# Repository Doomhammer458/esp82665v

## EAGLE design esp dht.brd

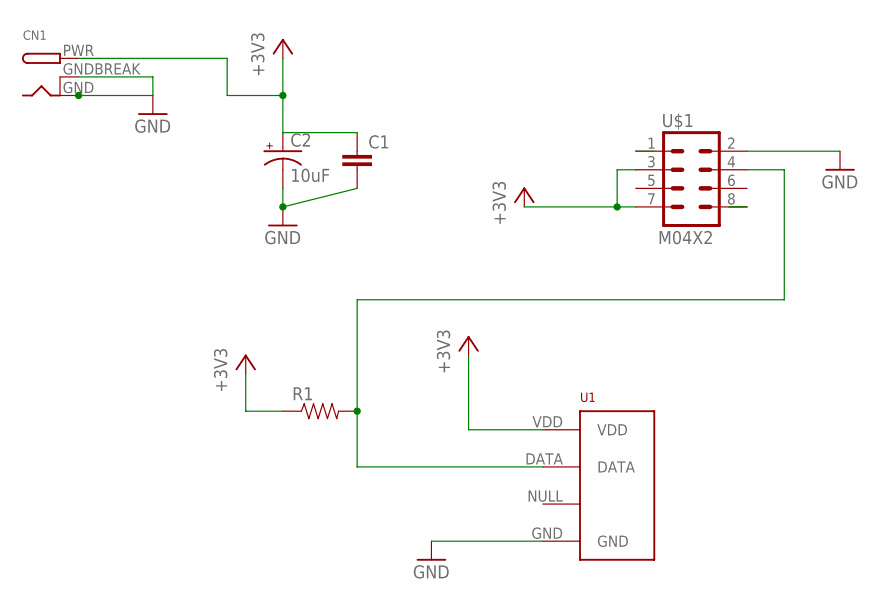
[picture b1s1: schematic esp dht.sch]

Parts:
C1: CAPPTH; CAP-PTH-SMALL
C2: 10uF; CPOL-RADIAL-10UF-25V
CN1: DCBARRELPTH; DCJACK_2MM_PTH
R1: RESISTORPTH-1/4W; AXIAL-0.4
U1: RHT03_DHT-22_AM2302RA; RHT03_DHT-22/RA
U$1: M04X2; 2X4

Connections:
+3V3: C1.1, C2.1 (+), CN1.PWR, R1.P$1 (1), U1.VDD, U$1.3, U$1.7
GND: C1.2, C2.2 (-), CN1.GND, CN1.GNDBREAK, U1.GND, U$1.2
unnamed: R1.P$2 (2), U1.DATA, U$1.4
TXL: U$1.1

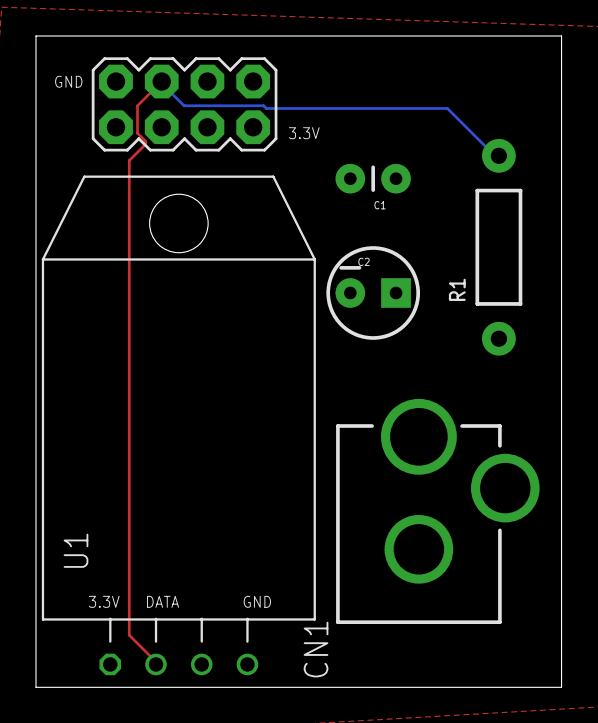
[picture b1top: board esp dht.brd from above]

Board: 2 copper layers, 29.2 x 36.2 mm, 6 parts (0 on the bottom side), 3 nets.

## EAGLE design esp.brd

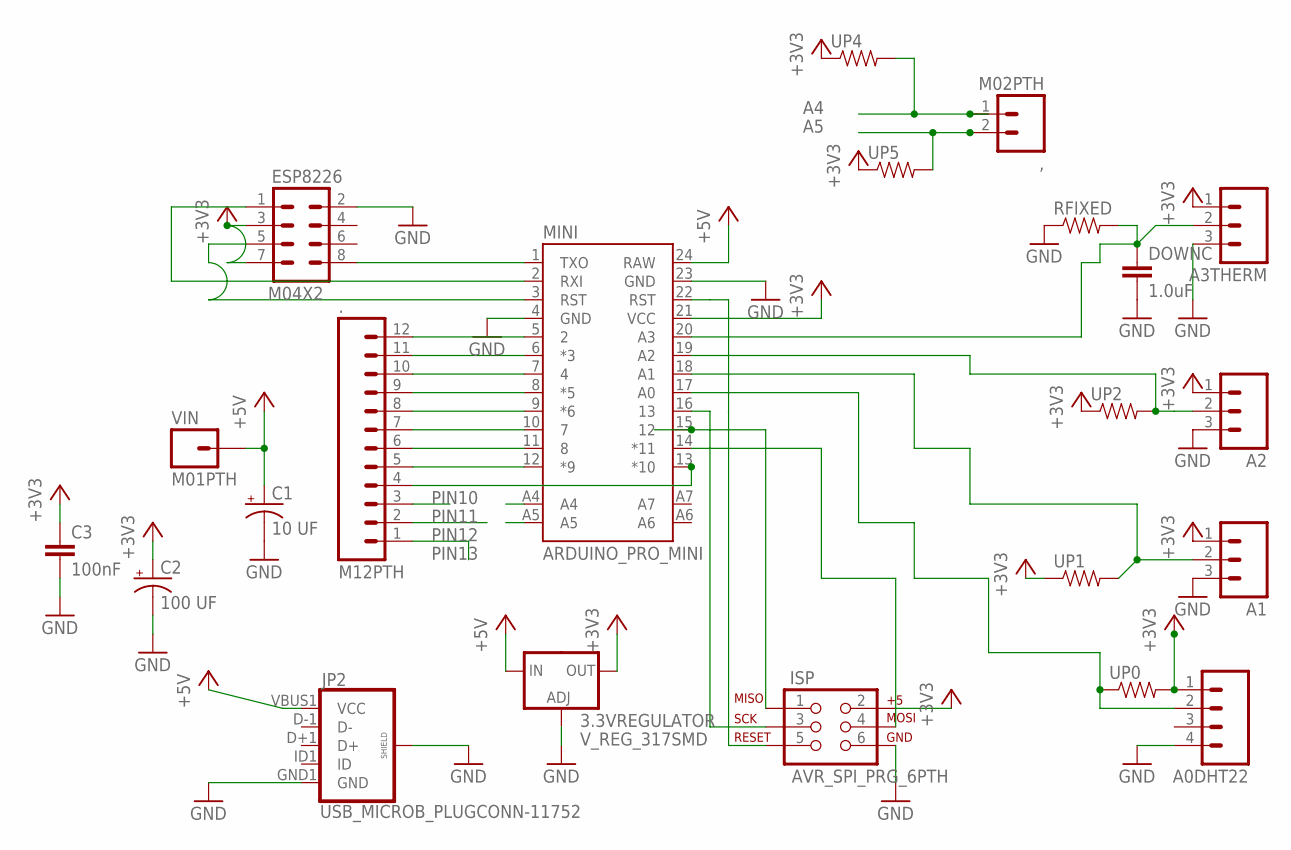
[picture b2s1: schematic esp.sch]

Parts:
3.3VREGULATOR: V_REG_317SMD; SOT223
,: M02PTH; 1X02
.: M12PTH; 1X12
A0DHT22: M04PTH; 1X04
A1, A2, A3THERM: M03PTH; 1X03
C1: 10 UF; CPOL-RADIAL-10UF-25V
C2: 100 UF; CPOL-RADIAL-10UF-25V
C3: 100nF; 0805
DOWNC: 1.0uF; 0805
ESP8226: M04X2; 2X4
ISP: AVR_SPI_PRG_6PTH; 2X3
JP2: USB_MICROB_PLUGCONN-11752; USB-B-MICRO-SMD_V03
MINI: ARDUINO_PRO_MINI
RFIXED: 0.3OHM-1/8W-1%(0805); 0805
UP0, UP1, UP2, UP4, UP5: 0.3OHM-1/8W-1%(0805); 0805
VIN: M01PTH; 1X01

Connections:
+3V3: 3.3VREGULATOR.2 (OUT), A0DHT22.1, A1.1, A2.1, A3THERM.1, C2.1 (+), C3.1, ESP8226.3, ESP8226.7, ISP.2, MINI.21 (VCC), UP0.2, UP1.1, UP2.1, UP4.1, UP5.1
+5V: 3.3VREGULATOR.3 (IN), C1.1 (+), JP2.VBUS1 (VCC), MINI.24 (RAW), VIN.1
A4: ,.1, MINI.A4, UP4.2
A5: ,.2, MINI.A5, UP5.2
GND: 3.3VREGULATOR.1 (ADJ), A0DHT22.4, A1.3, A2.3, A3THERM.3, C1.2 (-), C2.2 (-), C3.2, DOWNC.2, ESP8226.2, ISP.6, JP2.GND1 (GND), JP2.SHIELD1 (SHIELD), JP2.SHIELD2 (SHIELD), JP2.SHIELD3 (SHIELD), MINI.4 (GND), MINI.23 (GND), RFIXED.1
unnamed: ESP8226.1, MINI.2 (RXI)
unnamed: ESP8226.8, MINI.1 (TXO)
unnamed: A2.2, MINI.19 (A2), UP2.2
unnamed: A3THERM.2, DOWNC.1, MINI.20 (A3), RFIXED.2
unnamed: ..12, MINI.5 (2)
unnamed: A0DHT22.2, MINI.17 (A0), UP0.1
unnamed: ..11, MINI.6 (*3)
unnamed: ..10, MINI.7 (4)
unnamed: ..9, MINI.8 (*5)
unnamed: ..8, MINI.9 (*6)
unnamed: ..7, MINI.10 (7)
unnamed: ..6, MINI.11 (8)
unnamed: ..5, MINI.12 (*9)
unnamed: ESP8226.5, MINI.3 (RST)
unnamed: A1.2, MINI.18 (A1), UP1.2
PIN10: ..4, MINI.13 (*10)
PIN11: ..3, ISP.4, MINI.14 (*11)
PIN12: ..2, ISP.1, MINI.15 (12)
PIN13: ..1, ISP.3, MINI.16 (13)
RST: ISP.5, MINI.22 (RST)

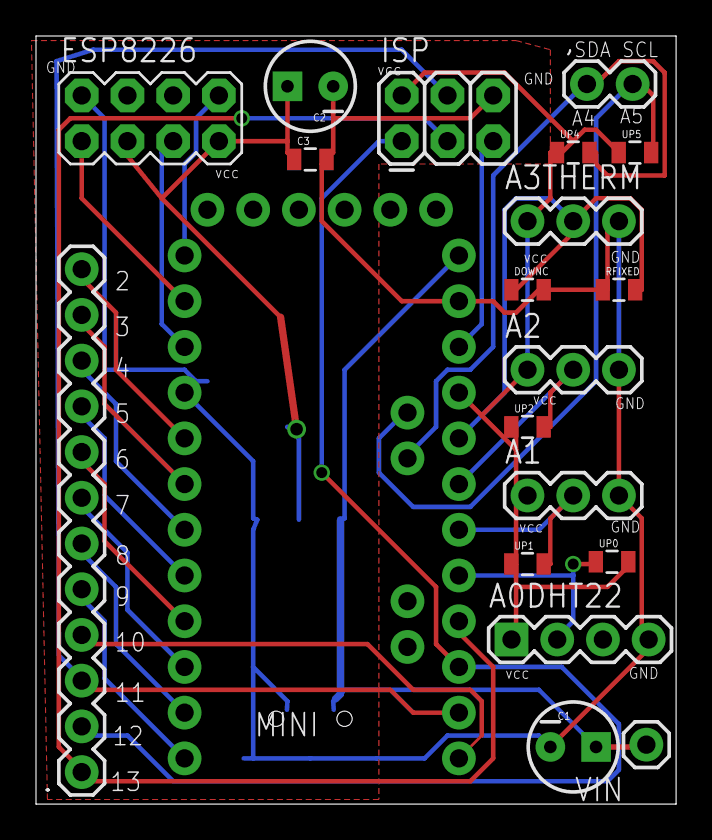
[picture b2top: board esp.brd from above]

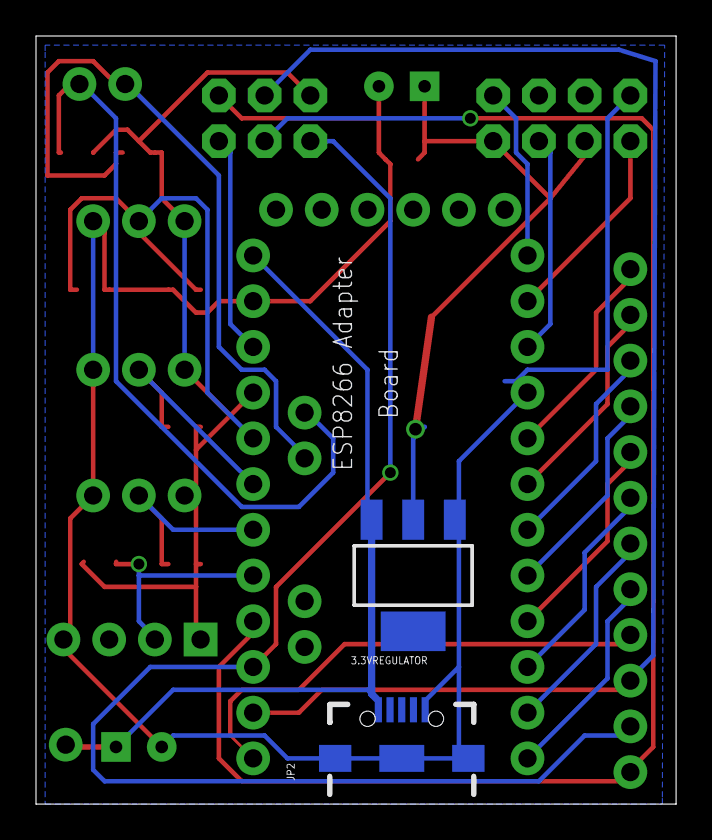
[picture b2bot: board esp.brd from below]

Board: 2 copper layers, 35.6 x 42.7 mm, 22 parts (2 on the bottom side), 25 nets.

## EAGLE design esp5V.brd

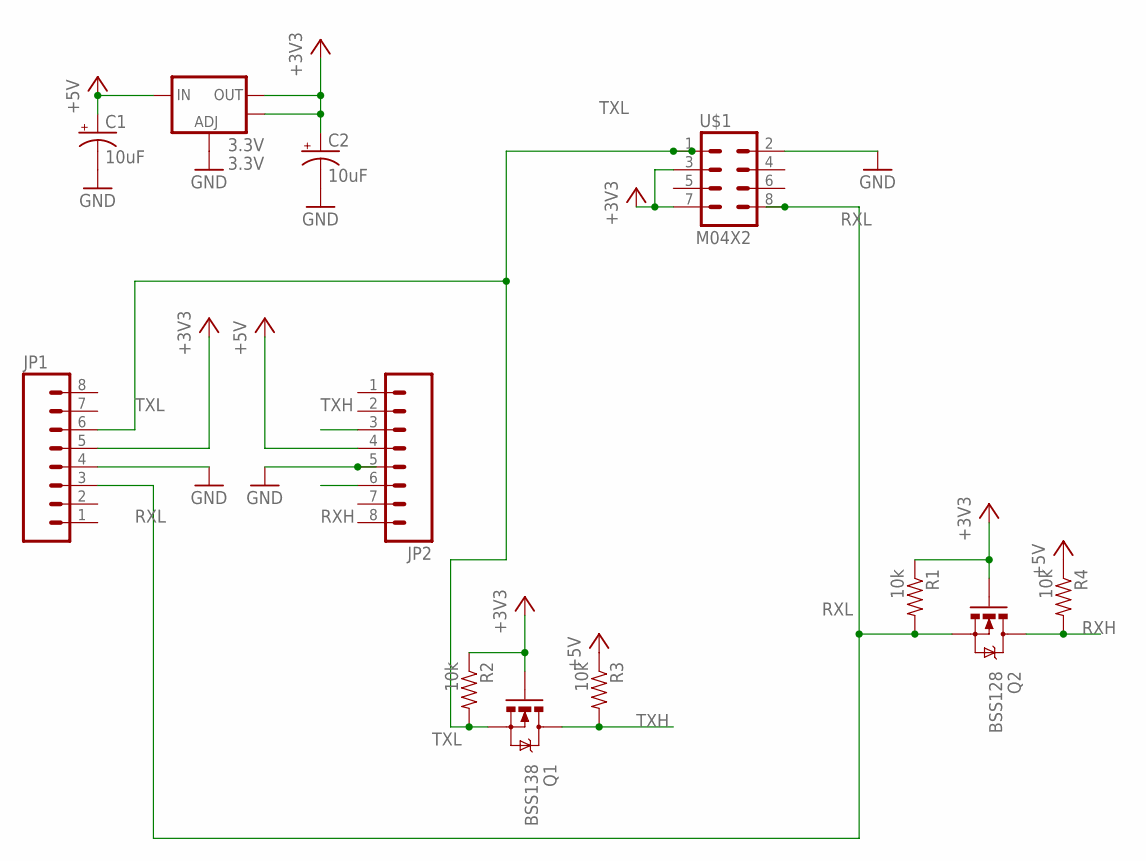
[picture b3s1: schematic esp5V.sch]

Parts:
3.3V: 3.3V; SOT223
C1, C2: 10uF; EIA3216
JP1, JP2: M08NO_SILK; 1X08_NO_SILK
Q1: BSS138; SOT23-3
Q2: BSS128; SOT23-3
R1, R2, R3, R4: 10k; 0805
U$1: M04X2; 2X4

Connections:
+3V3: 3.3V.2 (OUT), 3.3V.4 (OUT), C2.A (+), JP1.5, Q1.1 (G), Q2.1 (G), R1.1, R2.1, U$1.3, U$1.7
+5V: 3.3V.3 (IN), C1.A (+), JP2.4, R3.1, R4.1
GND: 3.3V.1 (ADJ), C1.C (-), C2.C (-), JP1.4, JP2.5, U$1.2
RXH: JP2.6, Q2.3 (D), R4.2
RXL: JP1.3, Q2.2 (S), R1.2, U$1.8
TXH: JP2.3, Q1.3 (D), R3.2
TXL: JP1.6, Q1.2 (S), R2.2, U$1.1

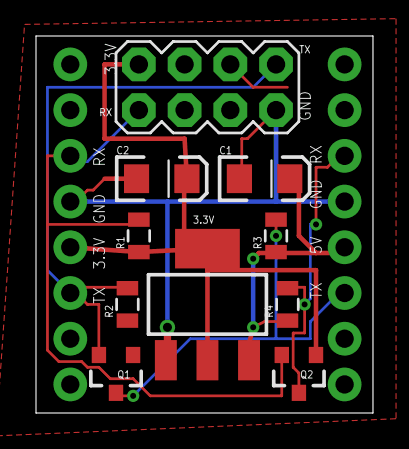
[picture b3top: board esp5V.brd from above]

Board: 2 copper layers, 18.7 x 20.9 mm, 12 parts (0 on the bottom side), 7 nets.

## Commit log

2014-12-08 board file
2015-03-06 added more boards and BOM
2015-03-06 updated BoM
2015-03-06 BoM / board update
2015-03-06 removed working files
2015-05-23 added DHT board

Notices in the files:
parts and their libraries:
SparkFun-Connectors: Licensing: Creative Commons ShareAlike 4.0 International - https://creativecommons.org/licenses/by-sa/4.0
